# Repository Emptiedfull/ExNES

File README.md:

# ExNES: Custom Nes Console

This is a custom built replica(more like modern copy) of the orignal nintendo console NES, including a custom made emulator in golang running on a raspberry pi along with two custom built wireless controllers and custom made cases for the components.

## Emulator Details

The emulator files reside in [The following directory](emulatorCore)

The emulator is based on the orignal nes and has the following features currently:
- Cycle implementation of the 6502 instruction set including illegal opcodes tested with SST's
- Scanline accurate pixel processing unit for static screens
- Fully implemented joypad with easy controller hooks
- Html api endpoints for various debugging functions
- NRAM support

Features planned:
- Mapper support
- Loopy registers and scrolling
- Active live debugger with breakpoint support
- Cpu optimisations for common instructions

### Structure 

```text
├── emulatorCore/
│   ├── debug_server/        # Fastapi server for console debug tools
|         ├── static/        # Contains static files to be deployed on server
|         └── main.py        # Entry Point for Fastapi App    
│   ├── logs/                # General storage for various logs 
│   └── controls.go          # JoyPad Defination and functions
│   └── cpu.go               # Cpu struct defination and functions
|   └── disassembler.go      # Utilities for cpu debugging
|   └── display.go           # Entrypoint for debug and main screen writing functions
|   └── helpers.go           # Shorthand functions for bit operaions
|   └── Main.go              # Main entrypoint
|   └── Opcodes.go           # Complete opcode map for the 6502 instruction set
|   └── ppu.go               # Main functions for the pixel processing unit
|   └── ppuDebug.go          # Utilities for debugging the ppu
|   └── server.go            # Server entrypoint for the debug server
```
** The emulator core is currently incomplete and hence does not contain running instructions and documentation**

## Controller Details 

Custom designed controller with an esp32 microcontroller with a custom designed case

Features in place : 
- Esp32 devboard microcontroller with network enabled
- Tactile push buttons for in-game inputs
- Extra buttons for debugging and QOL support
- RGB indicator for connection status
- Rechargable 3.7V 400mAh LiPo Battery with 5V boost up 
- Exposed reset button connected directly to devboard
- Custom designed 2 layer pcb with ergonomic labels

The pcb design is complete and [Build Files](controller_kicad) and [Fabrication Files](Fab) are located here

Click here to view the full [Hardware Bill of Materials (BOM)](./controller_kicad/bom.csv).

The case will also be custom designed but is not currently complete

## Console Details 

The console is currently undeveloped but it has the following features planned
- Raspberry pi 2 zero brain for running emulator core
- Onboard buttons for quick actions such as pairing and reseting 
- Visual indicator for controller connections 
- Hdmi output compatiblity
- Custom designed enclosure with heatsink support 

Requirements for the console may change as development begins

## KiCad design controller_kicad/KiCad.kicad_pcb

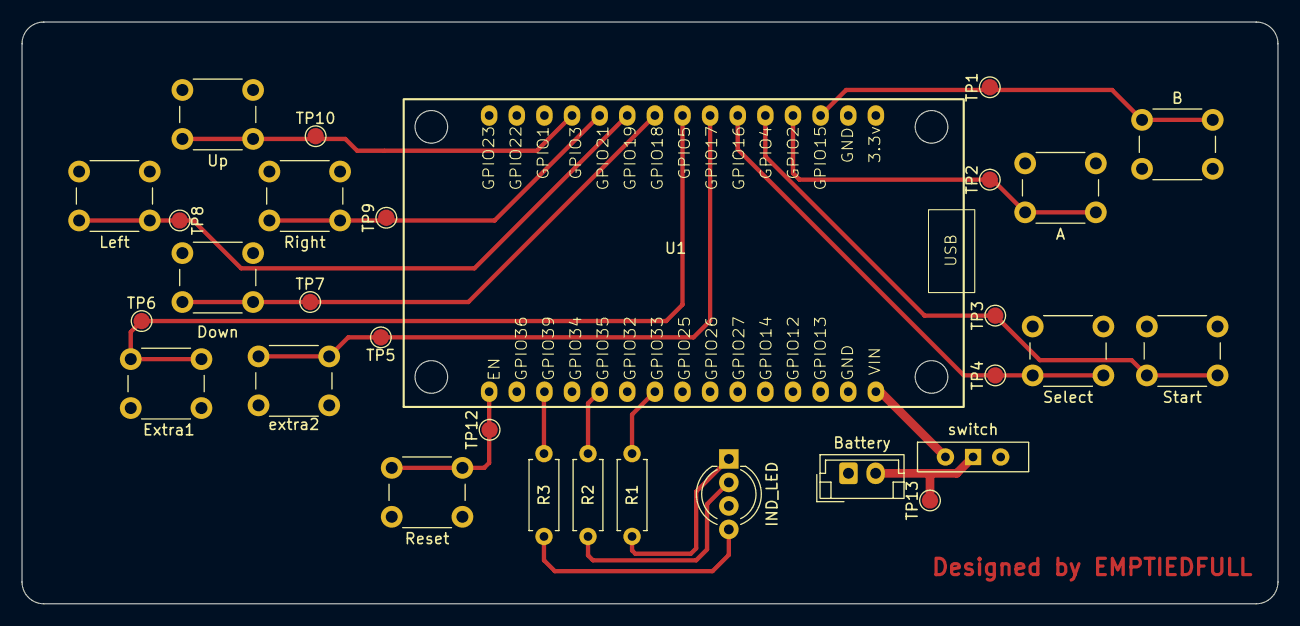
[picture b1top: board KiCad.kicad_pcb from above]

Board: 2 copper layers, 115.5 x 53.5 mm, 30 parts (0 on the bottom side), 20 nets.

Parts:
A: ButtonA; SW_PUSH_6mm_H5mm
B: ButtonB; SW_PUSH_6mm_H5mm
Battery: GRND; JST_EH_B2B-EH-A_1x02_P2.50mm_Vertical
Down: ButtonStart; SW_PUSH_6mm_H5mm
Extra1: Extra1; SW_PUSH_6mm_H5mm
IND_LED: LED_BGKR; LED_D5.0mm-4_RGB_Wide_Pins
Left: ButtonSelect; SW_PUSH_6mm_H5mm
R1, R2, R3: R; R_Axial_DIN0207_L6.3mm_D2.5mm_P7.62mm_Horizontal
Reset: Reset; SW_PUSH_6mm_H5mm
Right: Extra1; SW_PUSH_6mm_H5mm
Select: ButtonSelect; SW_PUSH_6mm_H5mm
Start: ButtonStart; SW_PUSH_6mm_H5mm
TP1, TP2, TP3, TP4, TP5, TP6, TP7, TP8, TP9, TP10, TP12, TP13: TestPoint; TestPoint_Pad_D1.5mm
U1: ESP32_30pin
Up: Extra2; SW_PUSH_6mm_H5mm
extra2: Extra2; SW_PUSH_6mm_H5mm
switch: SW_SPDT; SW_Slide-03_Wuerth-WS-SLTV_10x2.5x6.4_P2.54mm

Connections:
unnamed: A.2, B.2, Battery.1, Down.2, Extra1.2, IND_LED.3 (K), Left.2, Reset.1, Right.2, Select.2, Start.2, U1.2 (GND), Up.2, extra2.2
unnamed: Battery.2, TP13.1 (1_1), switch.1 (A)
unnamed: IND_LED.1 (BA), R1.2
unnamed: IND_LED.2 (GA), R2.2
unnamed: IND_LED.4 (RA), R3.2
unnamed: U1.1 (VIN), switch.2 (B)
unnamed: Reset.2, TP12.1 (1_1), U1.15 (EN)
unnamed: A.1, TP2.1 (1_1), U1.19 (GPIO2)
unnamed: TP10.1 (1_1), U1.27 (GPIO3), Up.1
unnamed: Start.1, TP3.1 (1_1), U1.20 (GPIO4)
unnamed: Extra1.1, TP6.1 (1_1), U1.23 (GPIO5)
unnamed: B.1, TP1.1 (1_1), U1.18 (GPIO15)
unnamed: Select.1, TP4.1 (1_1), U1.21 (GPIO16)
unnamed: TP5.1 (1_1), U1.22 (GPIO17), extra2.1
unnamed: Down.1, TP7.1 (1_1), U1.24 (GPIO18)
unnamed: Left.1, TP8.1 (1_1), U1.25 (GPIO19)
unnamed: Right.1, TP9.1 (1_1), U1.26 (GPIO21)
unnamed: R1.1, U1.9 (GPIO33)
unnamed: R2.1, U1.11 (GPIO35)
unnamed: R3.1, U1.13 (GPIO39)

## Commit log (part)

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2026-05-15 initial
2026-05-15 more opcodes
2026-05-16 even more opcodes, 0xBX series reached
2026-05-16 even more opcodes, last series reached
2026-05-18 CPU COMPLETE
2026-05-20 ppu initial
2026-05-21 entering debug hell
2026-05-23 abondoning ppu dev for now
2026-05-24 test-framework
2026-05-26 yeah lowk even more opcoes, reached E7
2026-05-26 all tests passed
2026-05-26 moved arudiono folder in same repo
2026-05-31 debug added
2026-06-01 debug server
2026-06-01 chr viewer
2026-06-02 ppu runs
2026-06-03 controller-pcb added
2026-06-03 Update README with PCB design and images
    Added images and updated PCB design information in README.
2026-06-03 added bom
2026-06-04 socket support
2026-06-05 control n socket barely working
2026-06-06 project restructuring
2026-06-06 merged controller folder into main
2026-06-06 basic connectivity
2026-06-06 optimizations maybeidk stuff just dosent work really
2026-06-07 better debug utils
2026-06-09 more debug utils
2026-06-09 snapshots
2026-06-10 snapshot-web
2026-06-10 gave up on fixing cycles, added a patchup fix to stepcycles
2026-06-11 new firmware start
2026-06-11 better frame handling(like way better went from +- 10000 variation to +-2 variation of cycles
2026-06-12 NMIS FIXED THE EMULATOR CORE IS PERFECT NOW WOOOO
2026-06-12 switching to dot based rendering
2026-06-12 ppu switch complete-bugs remaining
2026-06-12 fetcherppu fixed
2026-06-12 all scrolling bugs fixed
2026-06-12 add nrom scrolling games should work fine now
2026-06-12 retired the single state tests
2026-06-12 mapper0
2026-06-13 mapper 2 running
2026-06-13 mapper-1 support
2026-06-13 failed tries at debugging
2026-06-13 more failures
2026-06-13 still debugging the same thing
2026-06-13 remove reduncies
2026-06-14 ppu-cpu cycle ratio fixed
2026-06-14 more tries for debugging ppu nmi timings
2026-06-14 prg ram problems finally fixed- metroid running
2026-06-14 mapper 4 support initial
2026-06-14 project restructing n pruning extra files
2026-06-14 full replan
2026-06-14 error fixes
2026-06-14 structure for wasm
2026-06-14 wasm server
2026-06-14 messing around with wasm
2026-06-14 basic wasm
2026-06-14 switched to tinygo compilation
2026-06-14 added wasm visuals
2026-06-15 constant 60 fps wasm output
2026-06-15 frontend start tv done
2026-06-15 absurd nes console lol
2026-06-15 console complete
2026-06-15 frontend graphics done
2026-06-15 rom-select-menu
2026-06-15 rom caruosel
2026-06-15 multiplayer support(backend)
2026-06-16 rom slottin
2026-06-16 loading animations and touchups
2026-06-16 userflow complete
2026-06-16 small deco changes + rom loading facility
2026-06-17 more animations and tweaks
2026-06-17 knob settings
2026-06-17 controller graphics
2026-06-17 controller major done
2026-06-17 controller done
2026-06-18 savestate before massive chnages
2026-06-18 responsiveness
2026-06-18 apu start
2026-06-18 triangle n noise channels
2026-06-18 apu prototype done
2026-06-18 Reset point before audio driven shenanigans
2026-06-19 audio driven
2026-06-19 audiodriven (last commit was from wrong directory)
2026-06-19 complete audio driven+switched from oto to malgo
2026-06-19 wasm audio start
2026-06-19 buggy version
2026-06-20 switched to aduoi worklet
2026-06-20 ring buffer implementation change
2026-06-20 audio complete and working-bug fixes mostly
2026-06-21 new animations
2026-06-21 switched to web worker for wasm
2026-06-22 worklet + worker model added, syncing left
2026-06-22 bug fixes to worklet loop (working now) + added shared input buffer
2026-06-22 removed dead code and reorganized javascript files
2026-06-23 fileserver started: compile+compress added
2026-06-23 refactoring for esbuild support
2026-06-23 added esbuild minification and bundling
2026-06-24 basic compression n serving done
2026-06-24 added image n rom support-provider server complete
2026-06-25 dynamic game loading added + fixed navigation bar for game libraries
2026-06-25 hooked up the sound knob and added variable volume
2026-06-25 hooked the up the speed knob... kinda sound is fucked but idk what to do about it
2026-06-26 modals added
2026-06-26 added modal links with animations + added pause play and rom hotswap support is back(still gotta add buttons but yeh
2026-06-26 fixed a fuckass bug relating to swapping games
2026-06-26 fixed rom selection menu bug
2026-06-26 added the tip engine + a few tips
2026-06-27 setup for adding control updating
2026-06-27 renamed every fucking key and added some styling
2026-06-28 switched to a new icon library and added key animations for them
2026-06-28 added control changing
2026-06-29 added missing keys and fixed control updates
2026-06-29 changed pallete access to be branchless and hooked up pause button, also removed some logging calls
2026-06-30 snapshot for mappers + restrcuturing on the core
2026-06-30 complete restructuring of snapshot engine
2026-06-30 fixed snapshots to be zero alloc
2026-06-30 added wasm and worker communication for snapshot lists
